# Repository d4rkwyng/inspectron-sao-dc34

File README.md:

# INSPECTRON 34 — DC34 Meme TV SAO 📺

A DEF CON 34 Simple Add-On shaped like a retro CRT television that plays
looping meme GIFs on a 1.14" color IPS screen as TV *channels* — and hides
a puzzle game. Mount it as a USB drive and drag your own GIFs on. Channel
buttons surf memes (with TV static between channels, obviously).

**TUNE YOUR OWN SIGNAL.**

> ⚠️ **SPOILER WARNING** — `sitegen/` contains every puzzle answer
> (`CASES.md`, `gen_secrets.py`, `CHANNELS.md`). If you own an
> INSPECTRON 34 and want to solve
> [inspectron34.com](https://inspectron34.com) yourself, **stay out of
> `sitegen/`**.

## What it does

- **38 visible channels** of curated TV/movie/commercial memes on a Las
  Vegas-style dial — CH+/CH− surf, static wipe, channel bugs
- **"Declassify the Broadcast Authority"** — solve the case files at
  [inspectron34.com](https://inspectron34.com), dial answers on the
  device's FREQUENCY TUNER, and hidden channels come alive: dialed
  unlocks, station knocks, insider channels, trap frequencies, a
  badge-to-badge I2C handshake, and a Konami code
- **MASTER CONTROL menu** — TV guide, case-file progress, tuner, settings
  (brightness / standby / auto-scan / antenna LEDs / factory reset),
  about + QR
- Drop-your-own GIFs: shows up as a USB drive, `firmware/convert.py`
  preps anything ffmpeg can read

## Specs

- RP2040 + 16MB flash, CircuitPython 10 — mounts as a USB drive
- 1.14" 135x240 ST7789V IPS TFT (Newvisio N114-2413THBIG01-H13)
- Powered from the DC34 badge SAO port (3.0V!) or USB-C; auto power mux
- ~35–60mA from the badge — inside the DC34 100mA budget
- Buttons: CH+ / CH− / MODE, BOOT (UF2); antenna-tip LEDs on the SAO GPIOs
- SAO 1.69bis 2x3 header; designed for the badge's RIGHT port
  (spec-compliant with the 21mm inboard clearance rule)

## Highlights under the hood

- **Direct-render engine** (`firmware/fbdraw.py`): displayio's GIF
  pipeline was too slow on the RP2040 — frames go straight to the panel
  over SPI (CASET/RASET/RAMWR), all hot drawing in C via `bitmaptools`
- **The 264KB heap war**: a GIF decoder needs 88KB contiguous, the
  framebuffer 64KB — they *take turns*, with a pristine-heap boot preopen,
  slack reserves against fragmentation, and a framebuffer that degrades
  gracefully instead of crashing
- **Firmware ships precompiled** (`.mpy`): on-device compilation
  fragments the heap fatally; the drive's `code.py` is just `import app`
- **Spoiler-resistant unlocks**: the device carries only salted FNV-1a
  hashes — mounting the drive spoils nothing
- **Custom PCB router** (`hardware/pathfinder.py`): negotiated-congestion
  maze routing where Freerouting gave up
- **Factory tooling** (`test/`): golden-image flashing (~2 min/board,
  parallel daemon), device-side checksum verification
- **Desktop simulator** (`sim/`): runs the real `code.py` unmodified on
  pygame with ST7789/GRAM emulation

## Repo layout

- `firmware/` — CircuitPython app (player + game + menu + I2C badge
  target), GIF pipeline (`convert.py`), pin map (`pins.md` — source of
  truth), factory deploy tools
- `hardware/` — KiCad 10 project. The schematic was **generated** by
  `gen_sch.py` (netlist/BOM source of truth). **The PCB has extensive hand
  edits — do NOT re-run `gen_pcb.py`** (it would regenerate from stale
  tables and destroy the routed board; see ENGINEERING.md). `lib/` holds the
  custom TFT flex footprint.
- `site/` — the deployed puzzle site (answer-free, gated by
  `sitegen/check_no_answers.py`)
- `sitegen/` — site builders **+ ALL ANSWERS** ⚠️
- `memes/` / `secret/` — the channel packs (visible / hidden rewards)
- `sim/` — desktop simulator
- `test/` — factory flashing tools + quality gate
- `production/` — gerbers, BOM, pick-and-place, per revision
- `design/` — artwork sources and renders

## Gallery

| | | |
|---|---|---|
|  |  |  |
| Off any USB-C port, no badge needed | The dev rig: Pico H + Waveshare 1.14" (same ST7789) | The whole batch got its screens hand-soldered the night boards arrived |

Renders and artwork sources live in [`design/`](design/), including
[`render-assembled.png`](design/render-assembled.png).

## Flashing

See **[FLASHING.md](FLASHING.md)** — factory restore from the released
golden image, firmware-only updates, and building from source.

## Building / running

```bash
# simulator (no hardware needed) -- Python 3.9-3.13, see sim/requirements.txt
python3.13 -m venv sim/.venv && sim/.venv/bin/pip install -r sim/requirements.txt
sim/.venv/bin/python sim/run.py

# quality gate (lint + unit tests + boot smoke + answer-leak check + memory budget)
bash test/quality.sh

# flash a board (bootloader mode) from a captured golden image
bash test/golden-flash.sh
```

## Power budget notes (DC34 spec)

The badge supplies **3.0V, not 3.3V**, tested to 100mA across BOTH SAO
ports. All parts chosen for 2.7V+ operation. Backlight is PWM-dimmed and
defaults to 60%. Badge I2C bus (devices at 0x3C/0x19) is untouched — the
TFT hangs off the RP2040's own SPI, and GP0/GP1 to the badge bus serve a
badge.team-style descriptor at 0x50 (see `firmware/INTERFACING.md`).

## Credits

By **[@d4rkwyng](https://x.com/d4rkwyng)** — a
**[MINDTRICKS.IO](https://mindtricks.io)** production.
Prior SAOs: Mooncake (DC26), Mr. Meeseeks (DC26).
Spec: DEF CON 34 SAO Spec Sheet. Inspiration: Video Button SAO
(Ben Combee), TARS SAO (davedarko).

Code is MIT-licensed (see `LICENSE`). The meme GIFs are third-party
content included as parody/homage for a non-commercial community badge;
all trademarks and characters belong to their owners. Not affiliated with
DEF CON.

## Acknowledgments / third-party code

Full license notices for redistributed code: **[THIRD_PARTY_LICENSES.md](THIRD_PARTY_LICENSES.md)**.

- **[CircuitPython](https://circuitpython.org)** (MIT, © Adafruit
  Industries and contributors) — the runtime; the released golden image
  contains the CircuitPython 10.2.1 firmware build
- **[Adafruit_CircuitPython_ST7789](https://github.com/adafruit/Adafruit_CircuitPython_ST7789)**
  (MIT, © Adafruit Industries) — display init; a compiled copy is
  redistributed at `firmware/dist/lib/adafruit_st7789.mpy` and inside the
  golden image
- **[picotool](https://github.com/raspberrypi/picotool)** (BSD-3, ©
  Raspberry Pi) — referenced by the factory tooling (not redistributed)
- Dev/build dependencies: **Pillow**, **pygame**, **numpy**, **qrcode**
  (see `sim/requirements.txt`)
- The **DEF CON name and DC34 logo** belong to DEF CON Communications,
  Inc. — the logo appears on-device as community-badge homage
- The 5x7 pixel font in `fbdraw.py` is an original implementation of the
  classic public-domain 5x7 glyph pattern

Everything else — direct-render engine, puzzle/game code, PathFinder PCB
router, site, synthetic exhibits — is original to this project.

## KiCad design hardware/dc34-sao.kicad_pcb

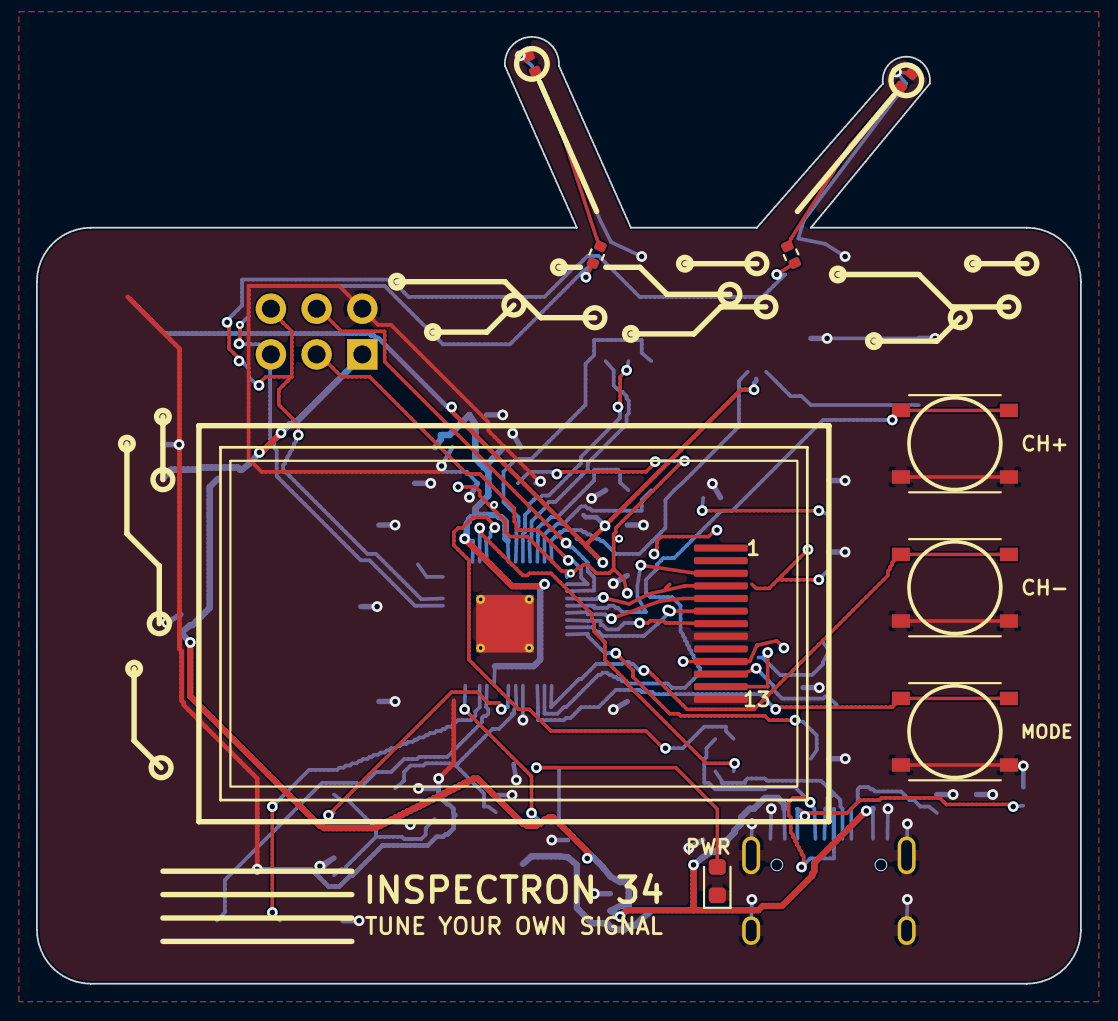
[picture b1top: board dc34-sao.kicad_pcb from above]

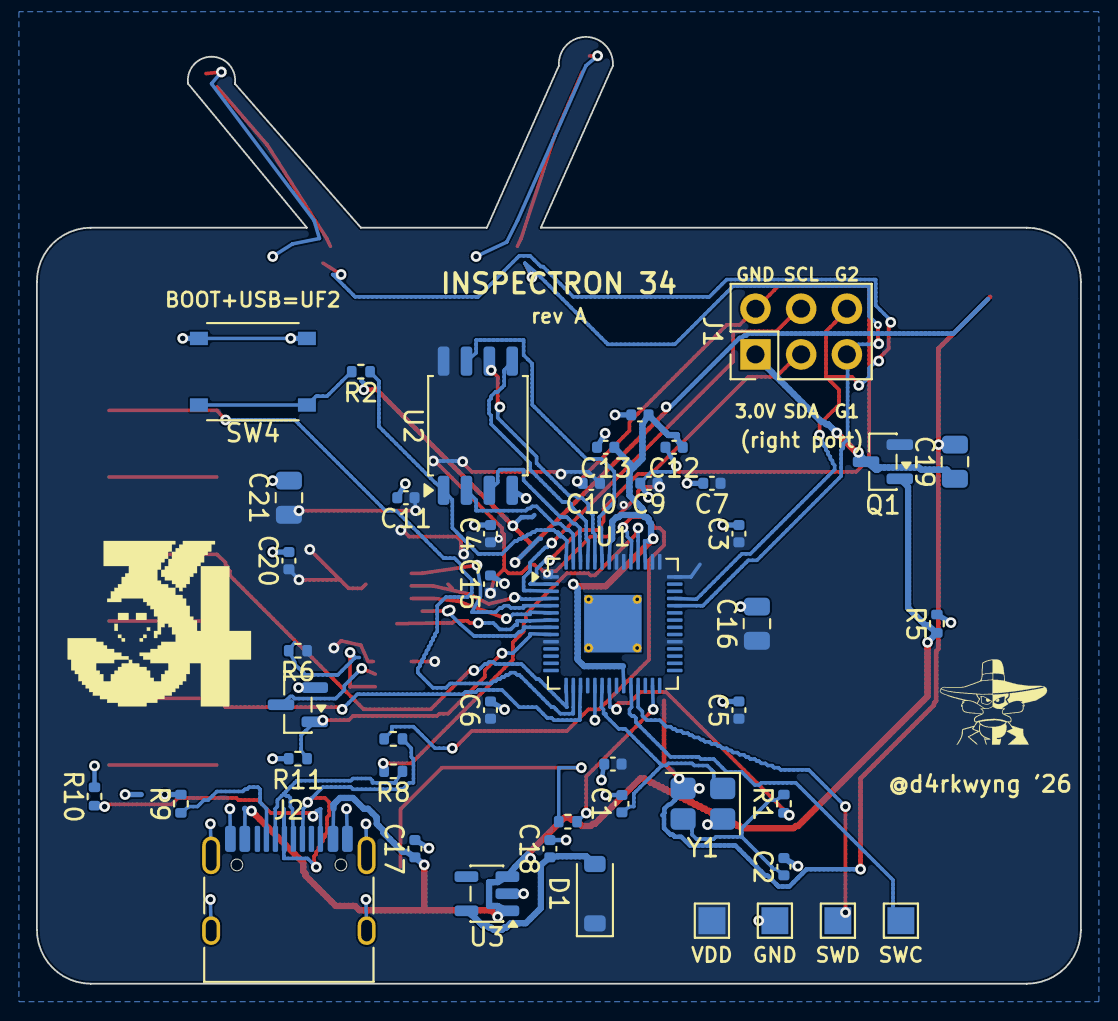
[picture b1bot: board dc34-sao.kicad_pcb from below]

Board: 2 copper layers, 58.0 x 52.6 mm, 56 parts (47 on the bottom side), 43 nets.

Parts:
C1, C2, C3, C4, C5, C6, C7, C8, C9, C10, C11, C12, C13, C14, C15, C17, C18, C20: C_0402_1005Metric
C16, C19, C21: C_0805_2012Metric
D1: D_SOD-123
G1: LOGO; d4rkwyng
G2: 34m; dc34_34skull_mid
J1: PinHeader_2x03_P2.54mm_Vertical
J2: USB_C_Receptacle_HRO_TYPE-C-31-M-12
J3: TFT_FPC_13P_N114
LED1: LED_0603_1608Metric
LED2, LED3: red; LED_0402_1005Metric
Q1, Q2: SOT-23
R1, R2, R3, R5, R6, R7, R8, R9, R10, R11: R_0402_1005Metric
R12, R13: 470R; R_0402_1005Metric
SW1, SW2, SW3, SW4: SW_TS-1187A
TP1, TP2, TP3, TP4: TestPoint_Pad_1.5x1.5mm
U1: QFN-56-1EP_7x7mm_P0.4mm_EP3.2x3.2mm_ThermalVias
U2: SOIC-8_5.3x5.3mm_P1.27mm
U3: SOT-23-5
Y1: Crystal_SMD_3225-4Pin_3.2x2.5mm

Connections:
ANT_L: LED2.2, R12.2
ANT_R: LED3.2, R13.2
BADGE_SCL: J1.4, U1.3
BADGE_SDA: J1.3, U1.2
BOOTSEL_SW: R2.2, SW4.1
BTN_CH_DOWN: SW1.1, U1.15
BTN_CH_UP: SW2.1, U1.16
BTN_MODE: SW3.1, U1.17
CC1: J2.A5, R9.1
CC2: J2.B5, R10.1
DVDD: C12.1, C13.1, C14.1, U1.23, U1.45, U1.50
GND: C1.2, C2.2, C3.2, C4.2, C5.2, C6.2, C7.2, C8.2, C9.2, C10.2, C11.2, C12.2, C13.2, C14.2, C15.2, C16.2, C17.2, C18.2, C19.2, C20.2, C21.2, J1.2, J2.A1, J2.A12, J2.B1, J2.B12, J2.SH, J3.8, J3.13, LED1.1, LED2.1, LED3.1, Q2.2, R5.2, R9.2, R10.2, R11.2, SW1.2, SW2.2, SW3.2, SW4.2, TP3.1, U1.19, U1.57, U2.4, U3.2, Y1.2, Y1.4
LED_A: LED1.2, R3.2
LED_PWR: R3.1, U1.27
QSPI_SCLK: U1.52, U2.6
QSPI_SD0: U1.53, U2.5
QSPI_SD1: U1.55, U2.2
QSPI_SD2: U1.54, U2.3
QSPI_SD3: U1.51, U2.7
QSPI_SS: R2.1, U1.56, U2.1
SAO_GPIO1: J1.5, R12.1, U1.38
SAO_GPIO2: J1.6, R13.1, U1.39
SWCLK: TP1.1, U1.24
SWDIO: TP2.1, U1.25
TFT_BL: Q2.1, R11.1, U1.9
TFT_CS: J3.7, U1.7
TFT_DC: J3.5, U1.6
TFT_LEDA: J3.12, R6.2
TFT_LEDK: J3.11, Q2.3
TFT_MOSI: J3.3, U1.5
TFT_RST: J3.6, U1.8
TFT_SCK: J3.4, U1.4
USB_C_DM: J2.A7, J2.B7, R8.1
USB_C_DP: J2.A6, J2.B6, R7.1
USB_DM: R8.2, U1.46
USB_DP: R7.2, U1.47
V33U: C18.1, D1.2, U3.5
VBUS: C17.1, J2.A4, J2.A9, J2.B4, J2.B9, Q1.1, R5.1, U3.1, U3.3
VDD: C3.1, C4.1, C5.1, C6.1, C7.1, C8.1, C9.1, C10.1, C11.1, C15.1, C16.1, C20.1, C21.1, D1.1, J3.10, Q1.2, R6.1, TP4.1, U1.1, U1.10, U1.22, U1.33, U1.42, U1.43, U1.44, U1.48, U1.49, U2.8
VSAO: C19.1, J1.1, Q1.3
XIN: C1.1, U1.20, Y1.1
XOUT: R1.1, U1.21
XTAL3: C2.1, R1.2, Y1.3

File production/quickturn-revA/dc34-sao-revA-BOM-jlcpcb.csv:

Comment,Designator,Footprint,LCSC Part #
33pF,"C1,C2",C_0402_1005Metric,C1562
100nF,"C3,C4,C5,C6,C7,C8,C9,C10,C11,C12,C13,C20",C_0402_1005Metric,C1525
1uF,"C14,C15,C17,C18",C_0402_1005Metric,C14445
10uF,"C16,C19,C21",C_0805_2012Metric,C440198
B5819W,D1,SOD-123,C8598
Header 2x3 2.54mm,J1,PinHeader_2x03_P2.54mm_Vertical,C65114
TYPE-C-31-M-12,J2,USB_C_Receptacle_HRO_TYPE-C-31-M-12,C165948
Green LED,LED1,LED_0603_1608Metric,C2289
Red LED,"LED2,LED3",LED_0402_1005Metric,C130719
AO3401A,Q1,SOT-23,C15127
AO3400A,Q2,SOT-23,C20917
1k,"R1,R2,R3",R_0402_1005Metric,C11702
100k,"R5,R11",R_0402_1005Metric,C25741
1R,R6,R_0402_1005Metric,C25086
27R,"R7,R8",R_0402_1005Metric,C25156
5.1k,"R9,R10",R_0402_1005Metric,C25905
470R,"R12,R13",R_0402_1005Metric,C25117
TS-1187A,"SW1,SW2,SW3,SW4",SW_TS-1187A,C318884
RP2040,U1,QFN-56-1EP_7x7mm_P0.4mm,C2040
W25Q128JVSIQ,U2,SOIC-8_5.3x5.3mm_P1.27mm,C97521
ME6211C33M5G-N,U3,SOT-23-5,C82942
12MHz,Y1,Crystal_SMD_3225-4Pin_3.2x2.5mm,C9002

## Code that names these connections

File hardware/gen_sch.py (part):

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        "27": "LED_PWR", "28": "NC", "29": "NC", "30": "NC", "31": "NC",
        "32": "NC", "34": "NC", "35": "NC", "36": "NC",
        "37": "NC",
        "38": "SAO_GPIO1", "39": "SAO_GPIO2",
        "40": "NC", "41": "NC",
        "43": "VDD", "44": "VDD", "45": "DVDD",
        "46": "USB_DM", "47": "USB_DP", "48": "VDD",
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     "Connector_PinHeader_2.54mm:PinHeader_2x03_P2.54mm_Vertical",
     "C65114", (40, 130), {
        "1": "VSAO", "2": "GND", "3": "BADGE_SDA", "4": "BADGE_SCL",
        "5": "SAO_GPIO1", "6": "SAO_GPIO2",
     }),
    # --- USB-C receptacle (USB2.0, 16 pin) ---
    ("J2", "Connector", "USB_C_Receptacle_USB2.0_16P", "TYPE-C-31-M-12",
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    ("LED3", "Device", "LED", "red", "LED_SMD:LED_0402_1005Metric",
     "C130719", (345, 190), {"1": "GND", "2": "ANT_R"}),
    ("R12", "Device", "R", "470R", FP_R, "", (330, 175),
     {"1": "SAO_GPIO1", "2": "ANT_L"}),
    ("R13", "Device", "R", "470R", FP_R, "", (330, 190),
     {"1": "SAO_GPIO2", "2": "ANT_R"}),
    # --- Decoupling / bulk ---
    ("C1", "Device", "C", "33pF", FP_C, "C1562", (135, 60),
     {"1": "XIN", "2": "GND"}),
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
